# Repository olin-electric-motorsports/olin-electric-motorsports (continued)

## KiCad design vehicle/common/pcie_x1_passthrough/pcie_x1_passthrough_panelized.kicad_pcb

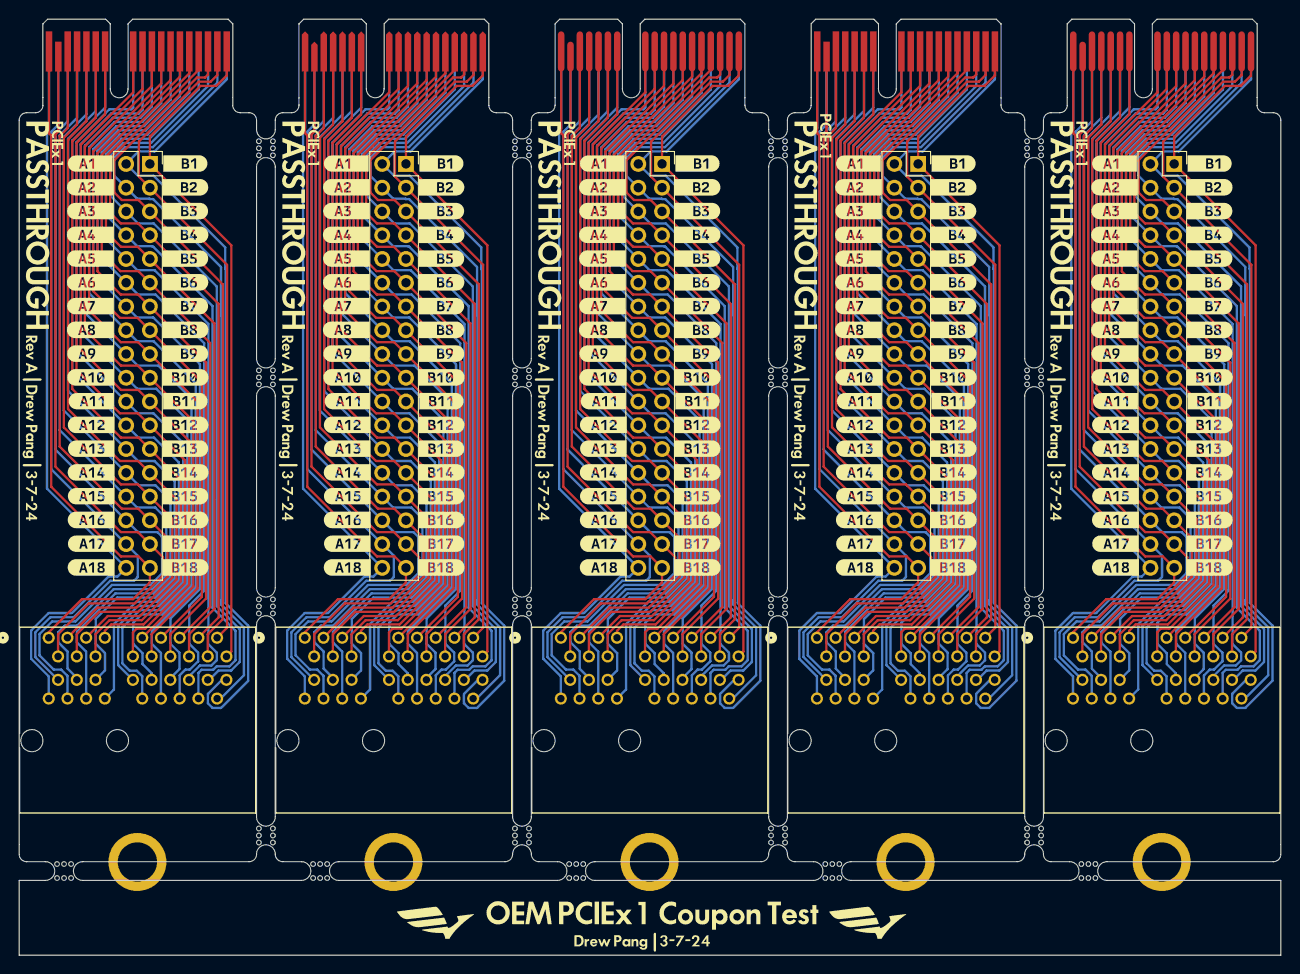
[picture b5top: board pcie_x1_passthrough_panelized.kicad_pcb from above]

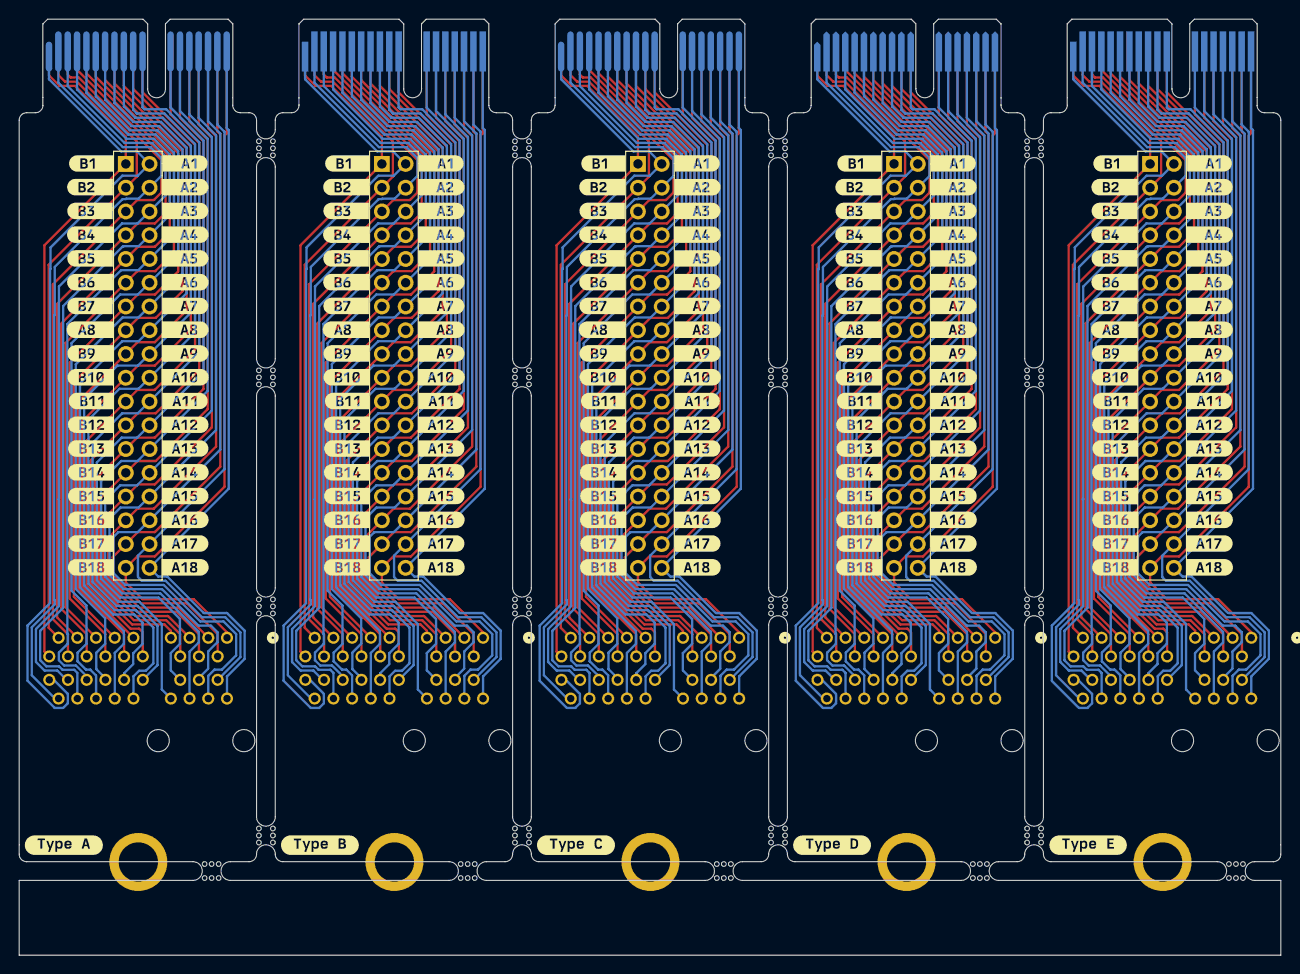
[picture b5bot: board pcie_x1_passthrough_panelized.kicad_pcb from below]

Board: 2 copper layers, 134.9 x 100.1 mm, 423 parts (190 on the bottom side), 36 nets.

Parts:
J1, J4, J8, J12, J16: pcie_x1_connector; pcie_x1_socket
J2, J2#2, J5, J6, J9, J10, J13, J14, J17, J18: Conn_02x18_Top_Bottom; PinSocket_2x18_P2.54mm_Vertical
J3, J7, J11, J11#2, J15: pcie_x1_connector; BUS_PCIexpress_x1
kibuzzard-65E1, kibuzzard-65E20, kibuzzard-65E39, kibuzzard-65E58, kibuzzard-65E96100: G***; kibuzzard-65E96100
kibuzzard-65E2, kibuzzard-65E21, kibuzzard-65E40, kibuzzard-65E59, kibuzzard-65E96303: G***; kibuzzard-65E96303
kibuzzard-65E3, kibuzzard-65E22, kibuzzard-65E41, kibuzzard-65E60, kibuzzard-65E96310: G***; kibuzzard-65E96310
kibuzzard-65E4, kibuzzard-65E23, kibuzzard-65E42, kibuzzard-65E61, kibuzzard-65E96314: G***; kibuzzard-65E96314
kibuzzard-65E5, kibuzzard-65E24, kibuzzard-65E43, kibuzzard-65E62, kibuzzard-65E96318: G***; kibuzzard-65E96318
kibuzzard-65E6, kibuzzard-65E25, kibuzzard-65E44, kibuzzard-65E63, kibuzzard-65E96322: G***; kibuzzard-65E96322
kibuzzard-65E7, kibuzzard-65E26, kibuzzard-65E45, kibuzzard-65E64, kibuzzard-65E96383: G***; kibuzzard-65E96383
kibuzzard-65E8, kibuzzard-65E27, kibuzzard-65E46, kibuzzard-65E65, kibuzzard-65E96396: G***; kibuzzard-65E96396
kibuzzard-65E9, kibuzzard-65E28, kibuzzard-65E47, kibuzzard-65E66, kibuzzard-65E96959: G***; kibuzzard-65E96959
kibuzzard-65E10, kibuzzard-65E29, kibuzzard-65E48, kibuzzard-65E67, kibuzzard-65E96962: G***; kibuzzard-65E96962
kibuzzard-65E11, kibuzzard-65E30, kibuzzard-65E49, kibuzzard-65E68, kibuzzard-65E96967: G***; kibuzzard-65E96967
kibuzzard-65E12, kibuzzard-65E31, kibuzzard-65E50, kibuzzard-65E69, kibuzzard-65E96973: G***; kibuzzard-65E96973
kibuzzard-65E13, kibuzzard-65E32, kibuzzard-65E51, kibuzzard-65E70, kibuzzard-65E96977: G***; kibuzzard-65E96977
kibuzzard-65E14, kibuzzard-65E33, kibuzzard-65E52, kibuzzard-65E71, kibuzzard-65E96980: G***; kibuzzard-65E96980
kibuzzard-65E15, kibuzzard-65E34, kibuzzard-65E53, kibuzzard-65E72, kibuzzard-65E96984: G***; kibuzzard-65E96984
kibuzzard-65E16, kibuzzard-65E35, kibuzzard-65E54, kibuzzard-65E73, kibuzzard-65E96989: G***; kibuzzard-65E96989
kibuzzard-65E17, kibuzzard-65E36, kibuzzard-65E55, kibuzzard-65E74, kibuzzard-65E96991: G***; kibuzzard-65E96991
kibuzzard-65E18, kibuzzard-65E37, kibuzzard-65E56, kibuzzard-65E75, kibuzzard-65E96995: G***; kibuzzard-65E96995
kibuzzard-65E19, kibuzzard-65E38, kibuzzard-65E57, kibuzzard-65E76, kibuzzard-65E96999: G***; kibuzzard-65E96999
kibuzzard-65E95D1, kibuzzard-65E95D2, kibuzzard-65E95D3, kibuzzard-65E95D4, kibuzzard-65E95D19: G***; kibuzzard-65E95D19
kibuzzard-65E95DA1, kibuzzard-65E95DA2, kibuzzard-65E95DA3, kibuzzard-65E95DA4, kibuzzard-65E95DA8: G***; kibuzzard-65E95DA8
kibuzzard-65E95DDF, kibuzzard-65E95DDF1, kibuzzard-65E95DDF2, kibuzzard-65E95DDF3, kibuzzard-65E95DDF4, kibuzzard-65E95DDF5, kibuzzard-65E95DDF6, kibuzzard-65E95DDF7, kibuzzard-65E95DDF8, kibuzzard-65E95DDF#2: G***; kibuzzard-65E95DDF
kibuzzard-65E95DE1, kibuzzard-65E95DE2, kibuzzard-65E95DE3, kibuzzard-65E95DE4, kibuzzard-65E95DE5: G***; kibuzzard-65E95DE4
kibuzzard-65E95DEB, kibuzzard-65E95DEB1, kibuzzard-65E95DEB2, kibuzzard-65E95DEB3, kibuzzard-65E95DEB4: G***; kibuzzard-65E95DEB
kibuzzard-65E95DEF, kibuzzard-65E95DEF1, kibuzzard-65E95DEF2, kibuzzard-65E95DEF3, kibuzzard-65E95DEF4: G***; kibuzzard-65E95DEF
kibuzzard-65E95DF1, kibuzzard-65E95DF3, kibuzzard-65E95DF4, kibuzzard-65E95DF6, kibuzzard-65E95DF9: G***; kibuzzard-65E95DF3
kibuzzard-65E95DF2, kibuzzard-65E95DF5, kibuzzard-65E95DF7, kibuzzard-65E95DF8, kibuzzard-65E95DF10: G***; kibuzzard-65E95DF8
kibuzzard-65E95DFB, kibuzzard-65E95DFB1, kibuzzard-65E95DFB2, kibuzzard-65E95DFB3, kibuzzard-65E95DFB4: G***; kibuzzard-65E95DFB
kibuzzard-65E95E1, kibuzzard-65E95E4, kibuzzard-65E95E04, kibuzzard-65E95E7, kibuzzard-65E95E10: G***; kibuzzard-65E95E04
kibuzzard-65E95E2, kibuzzard-65E95E5, kibuzzard-65E95E8, kibuzzard-65E95E11, kibuzzard-65E95E93: G***; kibuzzard-65E95E93
kibuzzard-65E95E3, kibuzzard-65E95E6, kibuzzard-65E95E9, kibuzzard-65E95E12, kibuzzard-65E95E97: G***; kibuzzard-65E95E97
kibuzzard-65E95E8F, kibuzzard-65E95E8F1, kibuzzard-65E95E8F2, kibuzzard-65E95E8F3, kibuzzard-65E95E8F4: G***; kibuzzard-65E95E8F
kibuzzard-65E95E9B, kibuzzard-65E95E9B1, kibuzzard-65E95E9B2, kibuzzard-65E95E9B3, kibuzzard-65E95E9B4: G***; kibuzzard-65E95E9B
kibuzzard-65E95E9E, kibuzzard-65E95E9E1, kibuzzard-65E95E9E2, kibuzzard-65E95E9E3, kibuzzard-65E95E9E4: G***; kibuzzard-65E95E9E
kibuzzard-65E95EA1, kibuzzard-65E95EA2, kibuzzard-65E95EA4, kibuzzard-65E95EA6, kibuzzard-65E95EA9: G***; kibuzzard-65E95EA2
kibuzzard-65E95EA3, kibuzzard-65E95EA5, kibuzzard-65E95EA7, kibuzzard-65E95EA8, kibuzzard-65E95EA10: G***; kibuzzard-65E95EA8
kibuzzard-65E95EAD, kibuzzard-65E95EAD1, kibuzzard-65E95EAD2, kibuzzard-65E95EAD3, kibuzzard-65E95EAD4: G***; kibuzzard-65E95EAD
kibuzzard-65E95F1, kibuzzard-65E95F2, kibuzzard-65E95F03, kibuzzard-65E95F3, kibuzzard-65E95F4: G***; kibuzzard-65E95F03
kibuzzard-65E960EE, kibuzzard-65E960EE1, kibuzzard-65E960EE2, kibuzzard-65E960EE3, kibuzzard-65E960EE4: G***; kibuzzard-65E960EE
kibuzzard-65E962FB, kibuzzard-65E962FB1, kibuzzard-65E962FB2, kibuzzard-65E962FB3, kibuzzard-65E962FB4: G***; kibuzzard-65E962FB
kibuzzard-65E962FE, kibuzzard-65E962FE1, kibuzzard-65E962FE2, kibuzzard-65E962FE3, kibuzzard-65E962FE4: G***; kibuzzard-65E962FE
kibuzzard-65E963A1, kibuzzard-65E963A3, kibuzzard-65E963A4, kibuzzard-65E963A6, kibuzzard-65E963A8: G***; kibuzzard-65E963A3
kibuzzard-65E963A2, kibuzzard-65E963A5, kibuzzard-65E963A7, kibuzzard-65E963A9, kibuzzard-65E963A10: G***; kibuzzard-65E963A9
kibuzzard-65E963AE, kibuzzard-65E963AE1, kibuzzard-65E963AE2, kibuzzard-65E963AE3, kibuzzard-65E963AE4: G***; kibuzzard-65E963AE
kibuzzard-65E969A0, kibuzzard-65E969A1, kibuzzard-65E969A3, kibuzzard-65E969A6, kibuzzard-65E969A8: G***; kibuzzard-65E969A0
kibuzzard-65E969A2, kibuzzard-65E969A4, kibuzzard-65E969A5, kibuzzard-65E969A7, kibuzzard-65E969A9: G***; kibuzzard-65E969A4
kibuzzard-65E969AA, kibuzzard-65E969AA1, kibuzzard-65E969AA2, kibuzzard-65E969AA3, kibuzzard-65E969AA4: G***; kibuzzard-65E969AA
kibuzzard-65E969AE, kibuzzard-65E969AE1, kibuzzard-65E969AE2, kibuzzard-65E969AE3, kibuzzard-65E969AE4: G***; kibuzzard-65E969AE
kibuzzard-65E969B1, kibuzzard-65E969B2, kibuzzard-65E969B4, kibuzzard-65E969B7, kibuzzard-65E969B9: G***; kibuzzard-65E969B1
kibuzzard-65E969B3, kibuzzard-65E969B5, kibuzzard-65E969B6, kibuzzard-65E969B8, kibuzzard-65E969B10: G***; kibuzzard-65E969B6
kibuzzard-65E969BA, kibuzzard-65E969BA1, kibuzzard-65E969BA2, kibuzzard-65E969BA3, kibuzzard-65E969BA4: G***; kibuzzard-65E969BA
kibuzzard-65E969BF, kibuzzard-65E969BF1, kibuzzard-65E969BF2, kibuzzard-65E969BF3, kibuzzard-65E969BF4: G***; kibuzzard-65E969BF
kibuzzard-65E969C1, kibuzzard-65E969C2, kibuzzard-65E969C4, kibuzzard-65E969C7, kibuzzard-65E969C9: G***; kibuzzard-65E969C2
kibuzzard-65E969C3, kibuzzard-65E969C5, kibuzzard-65E969C6, kibuzzard-65E969C8, kibuzzard-65E969C10: G***; kibuzzard-65E969C6
kibuzzard-65E969CA, kibuzzard-65E969CA1, kibuzzard-65E969CA2, kibuzzard-65E969CA3, kibuzzard-65E969CA4: G***; kibuzzard-65E969CA
kibuzzard-65E969CE, kibuzzard-65E969CE1, kibuzzard-65E969CE2, kibuzzard-65E969CE3, kibuzzard-65E969CE4: G***; kibuzzard-65E969CE
kibuzzard-65E969D1, kibuzzard-65E969D2, kibuzzard-65E969D4, kibuzzard-65E969D7, kibuzzard-65E969D9: G***; kibuzzard-65E969D2
kibuzzard-65E969D3, kibuzzard-65E969D5, kibuzzard-65E969D6, kibuzzard-65E969D8, kibuzzard-65E969D10: G***; kibuzzard-65E969D5
kibuzzard-65E969DA, kibuzzard-65E969DA1, kibuzzard-65E969DA2, kibuzzard-65E969DA3, kibuzzard-65E969DA4: G***; kibuzzard-65E969DA
kibuzzard-65E969DD, kibuzzard-65E969DD1, kibuzzard-65E969DD2, kibuzzard-65E969DD3, kibuzzard-65E969DD4: G***; kibuzzard-65E969DD
kibuzzard-65E969E1, kibuzzard-65E969E2, kibuzzard-65E969E6, kibuzzard-65E969E10, kibuzzard-65E969E13: G***; kibuzzard-65E969E1
kibuzzard-65E969E3, kibuzzard-65E969E5, kibuzzard-65E969E7, kibuzzard-65E969E11, kibuzzard-65E969E14: G***; kibuzzard-65E969E5
kibuzzard-65E969E4, kibuzzard-65E969E8, kibuzzard-65E969E9, kibuzzard-65E969E12, kibuzzard-65E969E15: G***; kibuzzard-65E969E9
kibuzzard-65E969ED, kibuzzard-65E969ED1, kibuzzard-65E969ED2, kibuzzard-65E969ED3, kibuzzard-65E969ED4: G***; kibuzzard-65E969ED
kibuzzard-65E981B7: G***; kibuzzard-65E981B7
kibuzzard-65E981F8: G***; kibuzzard-65E981F8
kibuzzard-65E981FF: G***; kibuzzard-65E981FF
kibuzzard-65E982B9: G***; kibuzzard-65E982B9
kibuzzard-65E9630A, kibuzzard-65E9630A1, kibuzzard-65E9630A2, kibuzzard-65E9630A3, kibuzzard-65E9630A4: G***; kibuzzard-65E9630A
kibuzzard-65E9633C, kibuzzard-65E9633C1, kibuzzard-65E9633C2, kibuzzard-65E9633C3, kibuzzard-65E9633C4: G***; kibuzzard-65E9633C
kibuzzard-65E9636C, kibuzzard-65E9636C1, kibuzzard-65E9636C2, kibuzzard-65E9636C3, kibuzzard-65E9636C4: G***; kibuzzard-65E9636C
kibuzzard-65E9638D, kibuzzard-65E9638D1, kibuzzard-65E9638D2, kibuzzard-65E9638D3, kibuzzard-65E9638D4: G***; kibuzzard-65E9638D
kibuzzard-65E9639B, kibuzzard-65E9639B1, kibuzzard-65E9639B2, kibuzzard-65E9639B3, kibuzzard-65E9639B4: G***; kibuzzard-65E9639B
kibuzzard-65E9639F, kibuzzard-65E9639F1, kibuzzard-65E9639F2, kibuzzard-65E9639F3, kibuzzard-65E9639F4: G***; kibuzzard-65E9639F
kibuzzard-65E9696D, kibuzzard-65E9696D1, kibuzzard-65E9696D2, kibuzzard-65E9696D3, kibuzzard-65E9696D4: G***; kibuzzard-65E9696D
kibuzzard-65E9697B, kibuzzard-65E9697B1, kibuzzard-65E9697B2, kibuzzard-65E9697B3, kibuzzard-65E9697B4: G***; kibuzzard-65E9697B
kibuzzard-65E9698D, kibuzzard-65E9698D1, kibuzzard-65E9698D2, kibuzzard-65E9698D3, kibuzzard-65E9698D4: G***; kibuzzard-65E9698D
kibuzzard-65E9699C, kibuzzard-65E9699C1, kibuzzard-65E9699C2, kibuzzard-65E9699C3, kibuzzard-65E9699C4: G***; kibuzzard-65E9699C
kibuzzard-65E98203: G***; kibuzzard-65E98203
kibuzzard-65E98207: G***; kibuzzard-65E98207
kibuzzard-65E98285: G***; kibuzzard-65E98285
mouse-bite-2mm-slot, mouse-bite-2mm-slot1, mouse-bite-2mm-slot2, mouse-bite-2mm-slot3, mouse-bite-2mm-slot4, mouse-bite-2mm-slot5, mouse-bite-2mm-slot6, mouse-bite-2mm-slot7, mouse-bite-2mm-slot8, mouse-bite-2mm-slot9, mouse-bite-2mm-slot10, mouse-bite-2mm-slot11, mouse-bite-2mm-slot12, mouse-bite-2mm-slot13, mouse-bite-2mm-slot14, mouse-bite-2mm-slot15, mouse-bite-2mm-slot15#2, mouse-bite-2mm-slot16, mouse-bite-2mm-slot17, mouse-bite-2mm-slot18, mouse-bite-2mm-slot19: VAL**; mouse-bite-2mm-slot

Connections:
/a1: J1.A1, J2.1, J3.A1, J4.A1, J5.1, J7.A1, J8.A1, J9.1, J11.A1, J12.A1, J13.1, J15.A1, J16.A1, J17.1
/a2: J1.A2, J2.2, J3.A2, J4.A2, J5.2, J7.A2, J8.A2, J9.2, J11.A2, J12.A2, J13.2, J15.A2, J16.A2, J17.2
/a3: J1.A3, J2.3, J3.A3, J4.A3, J5.3, J7.A3, J8.A3, J9.3, J11.A3, J12.A3, J13.3, J15.A3, J16.A3, J17.3
/a4: J1.A4, J2.4, J3.A4, J4.A4, J5.4, J7.A4, J8.A4, J9.4, J11.A4, J12.A4, J13.4, J15.A4, J16.A4, J17.4
/a5: J1.A5, J2.5, J3.A5, J4.A5, J5.5, J7.A5, J8.A5, J9.5, J11.A5, J12.A5, J13.5, J15.A5, J16.A5, J17.5
/a6: J1.A6, J2.6, J3.A6, J4.A6, J5.6, J7.A6, J8.A6, J9.6, J11.A6, J12.A6, J13.6, J15.A6, J16.A6, J17.6
/a7: J1.A7, J2.7, J3.A7, J4.A7, J5.7, J7.A7, J8.A7, J9.7, J11.A7, J12.A7, J13.7, J15.A7, J16.A7, J17.7
/a8: J1.A8, J2.8, J3.A8, J4.A8, J5.8, J7.A8, J8.A8, J9.8, J11.A8, J12.A8, J13.8, J15.A8, J16.A8, J17.8
/a9: J1.A9, J2.9, J3.A9, J4.A9, J5.9, J7.A9, J8.A9, J9.9, J11.A9, J12.A9, J13.9, J15.A9, J16.A9, J17.9
/a10: J1.A10, J2.10, J3.A10, J4.A10, J5.10, J7.A10, J8.A10, J9.10, J11.A10, J12.A10, J13.10, J15.A10, J16.A10, J17.10
/a11: J1.A11, J2.11, J3.A11, J4.A11, J5.11, J7.A11, J8.A11, J9.11, J11.A11, J12.A11, J13.11, J15.A11, J16.A11, J17.11
/a12: J1.A12, J2.12, J3.A12, J4.A12, J5.12, J7.A12, J8.A12, J9.12, J11.A12, J12.A12, J13.12, J15.A12, J16.A12, J17.12
/a13: J1.A13, J2.13, J3.A13, J4.A13, J5.13, J7.A13, J8.A13, J9.13, J11.A13, J12.A13, J13.13, J15.A13, J16.A13, J17.13
/a14: J1.A14, J2.14, J3.A14, J4.A14, J5.14, J7.A14, J8.A14, J9.14, J11.A14, J12.A14, J13.14, J15.A14, J16.A14, J17.14
/a15: J1.A15, J2.15, J3.A15, J4.A15, J5.15, J7.A15, J8.A15, J9.15, J11.A15, J12.A15, J13.15, J15.A15, J16.A15, J17.15
/a16: J1.A16, J2.16, J3.A16, J4.A16, J5.16, J7.A16, J8.A16, J9.16, J11.A16, J12.A16, J13.16, J15.A16, J16.A16, J17.16
/a17: J1.A17, J2.17, J3.A17, J4.A17, J5.17, J7.A17, J8.A17, J9.17, J11.A17, J12.A17, J13.17, J15.A17, J16.A17, J17.17
/a18: J1.A18, J2.18, J3.A18, J4.A18, J5.18, J7.A18, J8.A18, J9.18, J11.A18, J12.A18, J13.18, J15.A18, J16.A18, J17.18
/b1: J1.B1, J2.19, J3.B1, J4.B1, J5.19, J7.B1, J8.B1, J9.19, J11.B1, J12.B1, J13.19, J15.B1, J16.B1, J17.19
/b2: J1.B2, J2.20, J3.B2, J4.B2, J5.20, J7.B2, J8.B2, J9.20, J11.B2, J12.B2, J13.20, J15.B2, J16.B2, J17.20
/b3: J1.B3, J2.21, J3.B3, J4.B3, J5.21, J7.B3, J8.B3, J9.21, J11.B3, J12.B3, J13.21, J15.B3, J16.B3, J17.21
/b4: J1.B4, J2.22, J3.B4, J4.B4, J5.22, J7.B4, J8.B4, J9.22, J11.B4, J12.B4, J13.22, J15.B4, J16.B4, J17.22
/b5: J1.B5, J2.23, J3.B5, J4.B5, J5.23, J7.B5, J8.B5, J9.23, J11.B5, J12.B5, J13.23, J15.B5, J16.B5, J17.23
/b6: J1.B6, J2.24, J3.B6, J4.B6, J5.24, J7.B6, J8.B6, J9.24, J11.B6, J12.B6, J13.24, J15.B6, J16.B6, J17.24
/b7: J1.B7, J2.25, J3.B7, J4.B7, J5.25, J7.B7, J8.B7, J9.25, J11.B7, J12.B7, J13.25, J15.B7, J16.B7, J17.25
/b8: J1.B8, J2.26, J3.B8, J4.B8, J5.26, J7.B8, J8.B8, J9.26, J11.B8, J12.B8, J13.26, J15.B8, J16.B8, J17.26
/b9: J1.B9, J2.27, J3.B9, J4.B9, J5.27, J7.B9, J8.B9, J9.27, J11.B9, J12.B9, J13.27, J15.B9, J16.B9, J17.27
/b10: J1.B10, J2.28, J3.B10, J4.B10, J5.28, J7.B10, J8.B10, J9.28, J11.B10, J12.B10, J13.28, J15.B10, J16.B10, J17.28
/b11: J1.B11, J2.29, J3.B11, J4.B11, J5.29, J7.B11, J8.B11, J9.29, J11.B11, J12.B11, J13.29, J15.B11, J16.B11, J17.29
/b12: J1.B12, J2.30, J3.B12, J4.B12, J5.30, J7.B12, J8.B12, J9.30, J11.B12, J12.B12, J13.30, J15.B12, J16.B12, J17.30
/b13: J1.B13, J2.31, J3.B13, J4.B13, J5.31, J7.B13, J8.B13, J9.31, J11.B13, J12.B13, J13.31, J15.B13, J16.B13, J17.31
/b14: J1.B14, J2.32, J3.B14, J4.B14, J5.32, J7.B14, J8.B14, J9.32, J11.B14, J12.B14, J13.32, J15.B14, J16.B14, J17.32
/b15: J1.B15, J2.33, J3.B15, J4.B15, J5.33, J7.B15, J8.B15, J9.33, J11.B15, J12.B15, J13.33, J15.B15, J16.B15, J17.33
/b16: J1.B16, J2.34, J3.B16, J4.B16, J5.34, J7.B16, J8.B16, J9.34, J11.B16, J12.B16, J13.34, J15.B16, J16.B16, J17.34
/b17: J1.B17, J2.35, J3.B17, J4.B17, J5.35, J7.B17, J8.B17, J9.35, J11.B17, J12.B17, J13.35, J15.B17, J16.B17, J17.35
/b18: J1.B18, J2.36, J3.B18, J4.B18, J5.36, J7.B18, J8.B18, J9.36, J11.B18, J12.B18, J13.36, J15.B18, J16.B18, J17.36

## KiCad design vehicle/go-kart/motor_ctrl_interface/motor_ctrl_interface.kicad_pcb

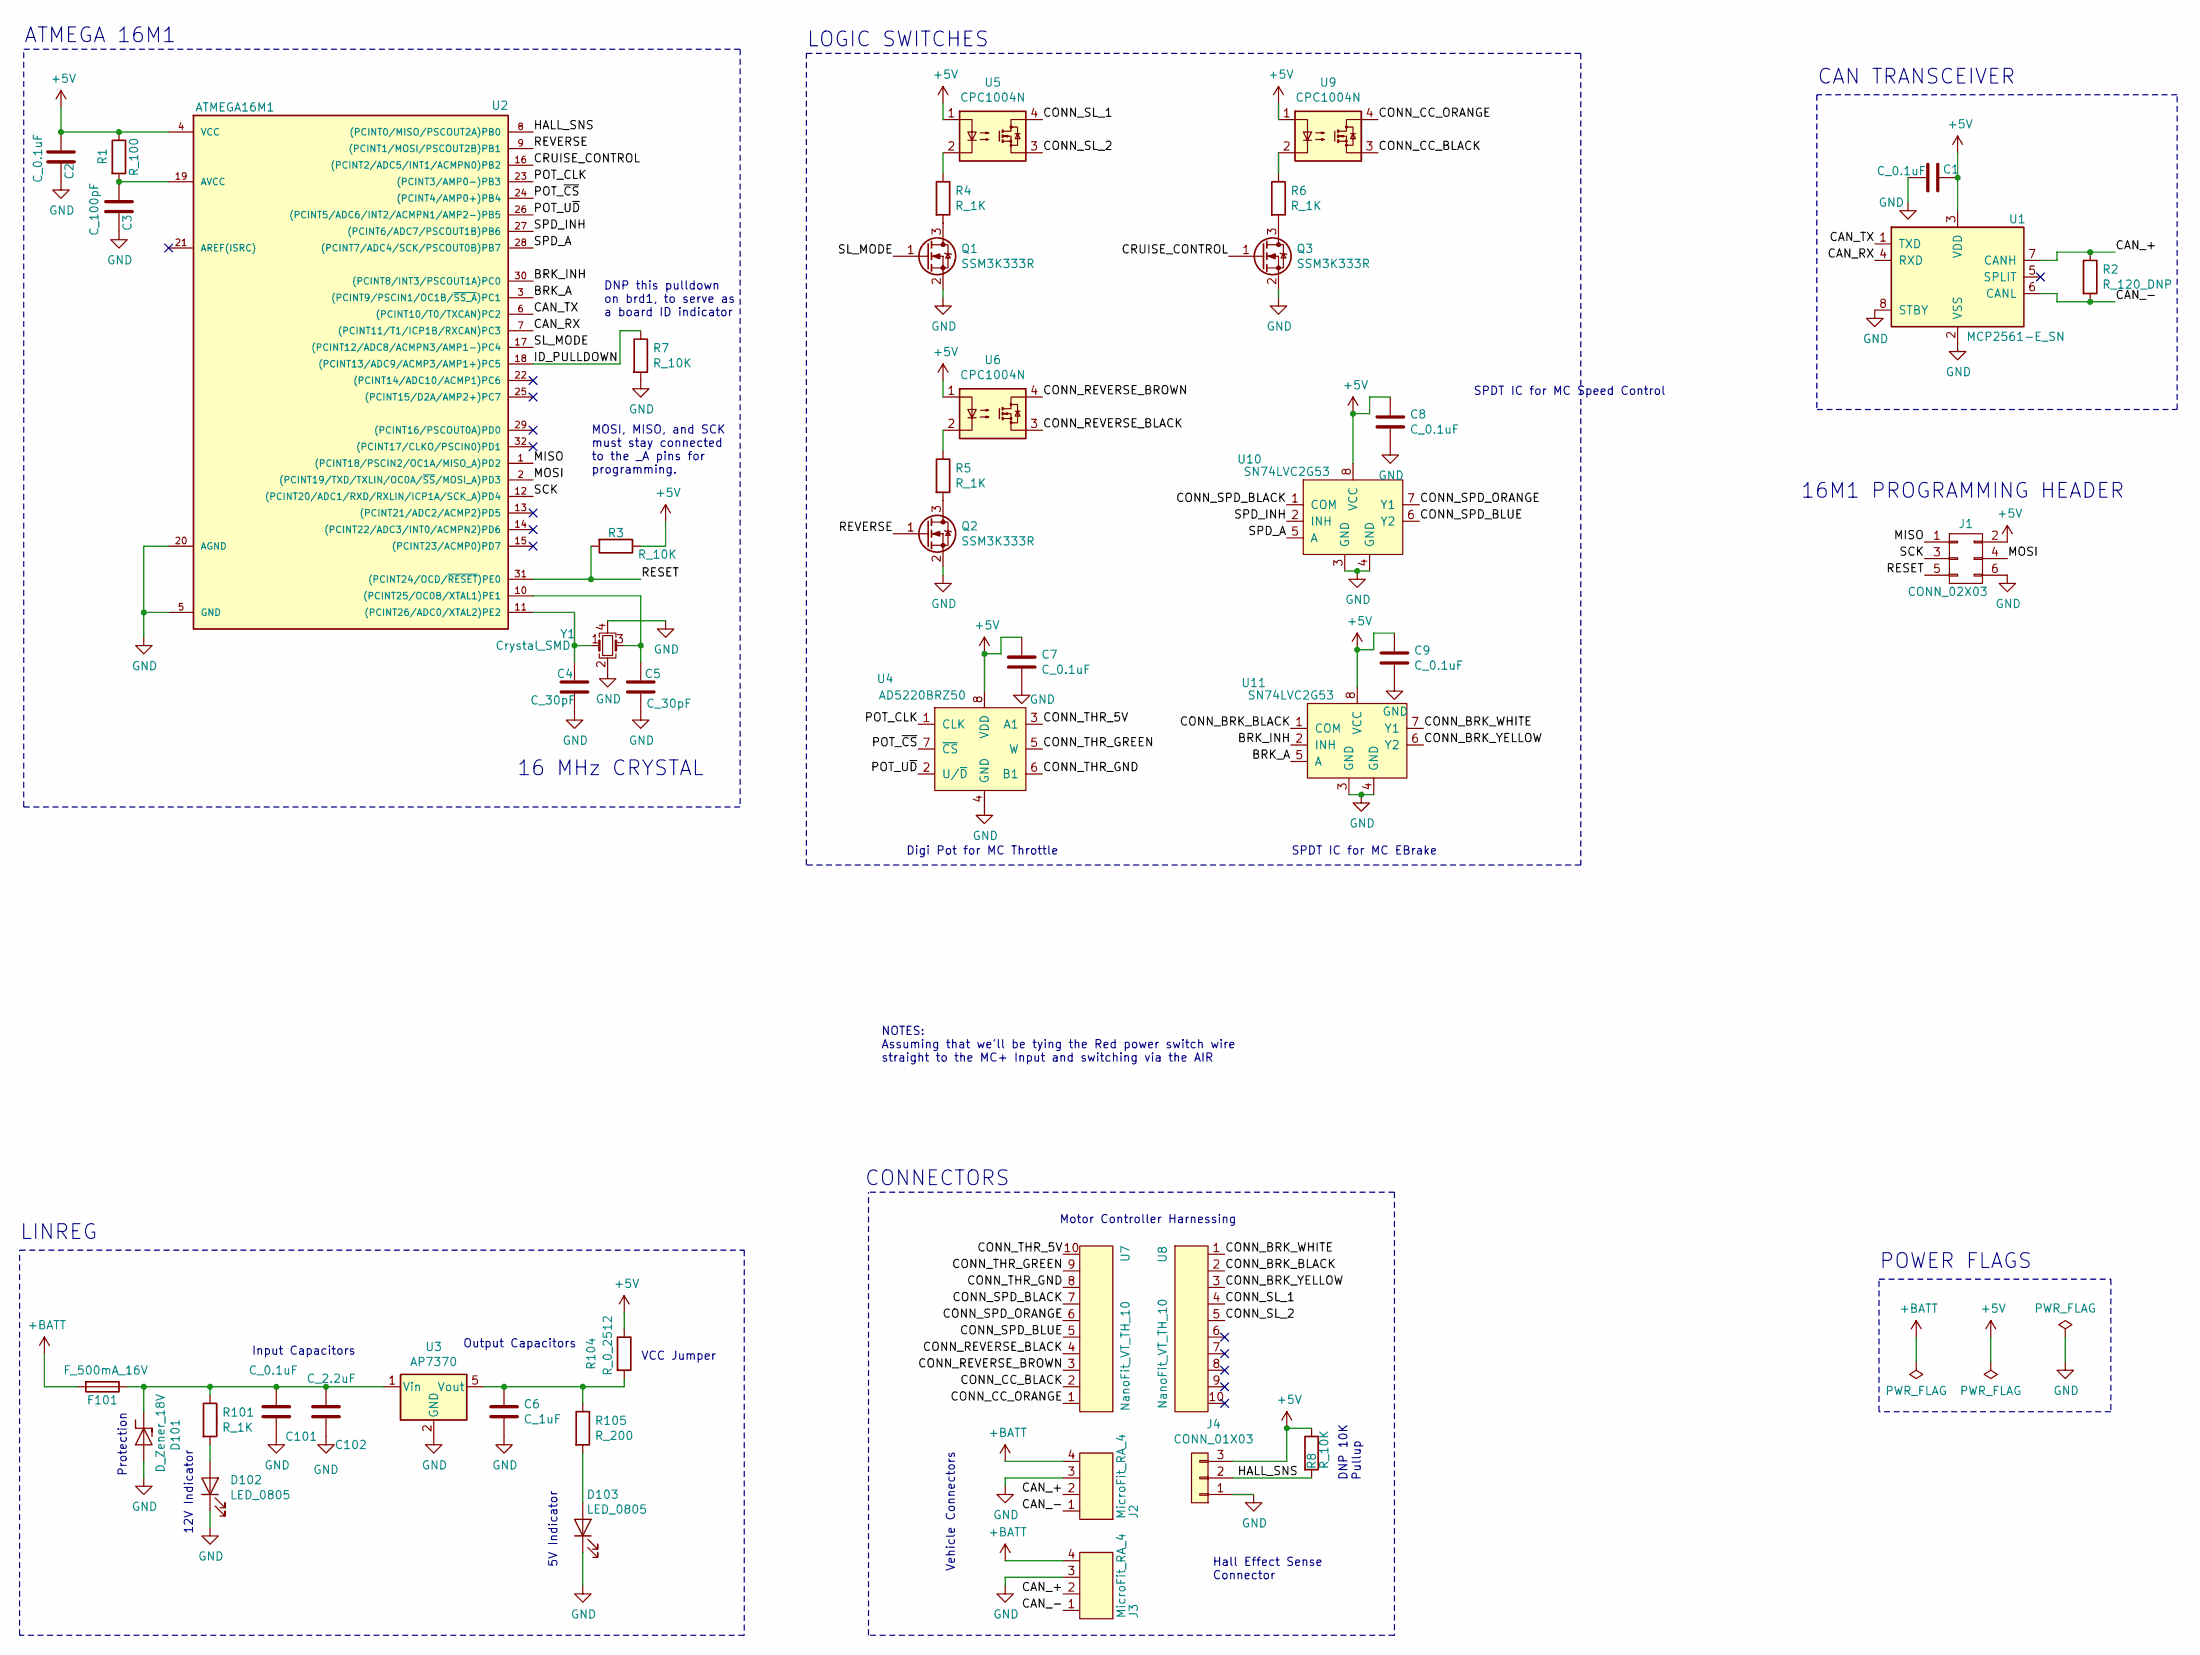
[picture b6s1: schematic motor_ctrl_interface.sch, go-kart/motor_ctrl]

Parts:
C1, C2, C7, C8, C9, C101: C_0.1uF; C_0805_OEM; MPN 478-3352-1-ND
C3: C_100pF; C_0805_OEM; MPN 732-7852-1-ND
C4, C5: C_30pF; C_0805_OEM; MPN 1276-1130-1-ND
C6: C_1uF; C_0805_OEM
C102: C_2.2uF; C_0603_1608Metric; MPN 311-1451-1-ND
D101: D_Zener_18V; DO-214AA; MPN SMBJ5355B-TPMSCT-ND
D102, D103: LED_0805; LED_0805_OEM; MPN 475-1410-1-ND
F101: F_500mA_16V; Fuse_1210; MPN 507-1786-1-ND
J1: CONN_02X03; Pin_Header_Straight_2x03; MPN 609-3234-ND
J2, J3: MicroFit_RA_4
J4: CONN_01X03; PinHeader_1x03_P2.54mm_Vertical; MPN 855-M20-9990346
Q1, Q2, Q3: SSM3K333R; SOT-23F; MPN SSM3K333RLFCT-ND
R1: R_100; R_0805_OEM; MPN RNCP0805FTD100RCT-ND
R2: R_120_DNP; R_0805_OEM; MPN 667-ERJ-6ENF1200V
R3, R7, R8: R_10K; R_0805_OEM; MPN CRS0805-FX-1002ELFCT-ND
R4, R5, R6, R101: R_1K; R_0805_OEM; MPN RNCP0805FTD1K00CT-ND
R104: R_0_2512; R_2512_OEM; MPN A121322CT-ND
R105: R_200; R_0805_OEM; MPN RMCF0805JT200RCT-ND
U1: MCP2561-E_SN; SOIC-8_3.9x4.9mm_Pitch1.27mm_OEM; MPN MCP2561-E/SN-ND
U2: ATMEGA16M1; TQFP-32_7x7mm_Pitch0.8mm; MPN ATMEGA16M1-AU-ND
U3: AP7370; SOT-23-5; MPN AP7370-50W5-7DICT-ND
U4: AD5220BRZ50; SOIC-8_3.9x4.9mm_Pitch1.27mm_OEM
U5, U6, U9: CPC1004N; SOP-4_3.8x4.1mm_P2.54mm
U7, U8: NanoFit_VT_TH_10; NanoFit_VT_10
U10, U11: SN74LVC2G53; MSOP-8_3x3mm_P0.65mm
Y1: Crystal_SMD; Crystal_SMD_FA238; MPN 887-1125-1-ND

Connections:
+5V: C1.1, C2.1, C7.1, C8.1, C9.1, J1.2, J4.3, R1.1, R3.1, R8.1, R104.1, U1.3 (VDD), U2.4 (VCC), U4.8 (VDD), U5.1, U6.1, U9.1, U10.8 (VCC), U11.8 (VCC)
+BATT: F101.2, J2.4, J3.4
/BRK_A: U2.3 ((PCINT9/PSCIN1/OC1B/~SS_A~)PC1), U11.5 (A)
/BRK_INH: U2.30 ((PCINT8/INT3/PSCOUT1A)PC0), U11.2 (INH)
/CAN_+: J2.2, J3.2, R2.1, U1.7 (CANH)
/CAN_-: J2.1, J3.1, R2.2, U1.6 (CANL)
/CAN_RX: U1.4 (RXD), U2.7 ((PCINT11/T1/ICP1B/RXCAN)PC3)
/CAN_TX: U1.1 (TXD), U2.6 ((PCINT10/T0/TXCAN)PC2)
/CONN_BRK_BLACK: U8.2, U11.1 (COM)
/CONN_BRK_WHITE: U8.1, U11.7 (Y1)
/CONN_BRK_YELLOW: U8.3, U11.6 (Y2)
/CONN_CC_BLACK: U7.2, U9.3
/CONN_CC_ORANGE: U7.1, U9.4
/CONN_REVERSE_BLACK: U6.3, U7.4
/CONN_REVERSE_BROWN: U6.4, U7.3
/CONN_SL_1: U5.4, U8.4
/CONN_SL_2: U5.3, U8.5
/CONN_SPD_BLACK: U7.7, U10.1 (COM)
/CONN_SPD_BLUE: U7.5, U10.6 (Y2)
/CONN_SPD_ORANGE: U7.6, U10.7 (Y1)
/CONN_THR_5V: U4.3 (A1), U7.10
/CONN_THR_GND: U4.6 (B1), U7.8
/CONN_THR_GREEN: U4.5 (W), U7.9
/CRUISE_CONTROL: Q3.1 (G), U2.16 ((PCINT2/ADC5/INT1/ACMPN0)PB2)
/HALL_SNS: J4.2, R8.2, U2.8 ((PCINT0/MISO/PSCOUT2A)PB0)
/ID_PULLDOWN: R7.1, U2.18 ((PCINT13/ADC9/ACMP3/AMP1+)PC5)
/MISO: J1.1, U2.1 ((PCINT18/PSCIN2/OC1A/MISO_A)PD2)
/MOSI: J1.4, U2.2 ((PCINT19/TXD/TXLIN/OC0A/~SS~/MOSI_A)PD3)
/POT_CLK: U2.23 ((PCINT3/AMP0-)PB3), U4.1 (CLK)
/POT_U~D: U2.26 ((PCINT5/ADC6/INT2/ACMPN1/AMP2-)PB5), U4.2 (U/~D)
/POT_~CS: U2.24 ((PCINT4/AMP0+)PB4), U4.7 (~CS)
/RESET: J1.5, R3.2, U2.31 ((PCINT24/OCD/~RESET~)PE0)
/REVERSE: Q2.1 (G), U2.9 ((PCINT1/MOSI/PSCOUT2B)PB1)
/SCK: J1.3, U2.12 ((PCINT20/ADC1/RXD/RXLIN/ICP1A/SCK_A)PD4)
/SL_MODE: Q1.1 (G), U2.17 ((PCINT12/ADC8/ACMPN3/AMP1-)PC4)
/SPD_A: U2.28 ((PCINT7/ADC4/SCK/PSCOUT0B)PB7), U10.5 (A)
/SPD_INH: U2.27 ((PCINT6/ADC7/PSCOUT1B)PB6), U10.2 (INH)
GND: C1.2, C2.2, C3.2, C4.2, C5.2, C6.2, C7.2, C8.2, C9.2, C101.2, C102.2, D101.2 (A), D102.1 (K), D103.1 (K), J1.6, J2.3, J3.3, J4.1, Q1.2 (S), Q2.2 (S), Q3.2 (S), R7.2, U1.2 (VSS), U1.8 (STBY), U2.5 (GND), U2.20 (AGND), U3.2 (GND), U4.4 (GND), U10.3 (GND), U10.4 (GND), U11.3 (GND), U11.4 (GND), Y1.2, Y1.4
unnamed: C3.1, R1.2, U2.19 (AVCC)
unnamed: C4.1, U2.11 ((PCINT26/ADC0/XTAL2)PE2), Y1.1
unnamed: C5.1, U2.10 ((PCINT25/OC0B/XTAL1)PE1), Y1.3
unnamed: C6.1, R104.2, R105.1, U3.5 (Vout)
unnamed: C101.1, C102.1, D101.1 (K), F101.1, R101.1, U3.1 (Vin)
unnamed: D102.2 (A), R101.2
unnamed: D103.2 (A), R105.2
unnamed: Q1.3 (D), R4.2
unnamed: Q2.3 (D), R5.2
unnamed: Q3.3 (D), R6.2
unnamed: R4.1, U5.2
unnamed: R5.1, U6.2
unnamed: R6.1, U9.2

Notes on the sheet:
Input Capacitors
12V Indicator
Protection
LINREG
Output Capacitors
VCC Jumper
5V Indicator
CAN TRANSCEIVER
ATMEGA 16M1
16 MHz CRYSTAL
POWER FLAGS
16M1 PROGRAMMING HEADER
MOSI, MISO, and SCK must stay connected to the _A pins for programming.
Digi Pot for MC Throttle
SPDT IC for MC Speed Control
SPDT IC for MC EBrake
Motor Controller Harnessing
Vehicle Connectors
CONNECTORS
LOGIC SWITCHES
DNP 10K Pullup
Hall Effect Sense Connector
NOTES: Assuming that we'll be tying the Red power switch wire straight to the MC+ Input and switching via the AIR
DNP this pulldown on brd1, to serve as a board ID indicator

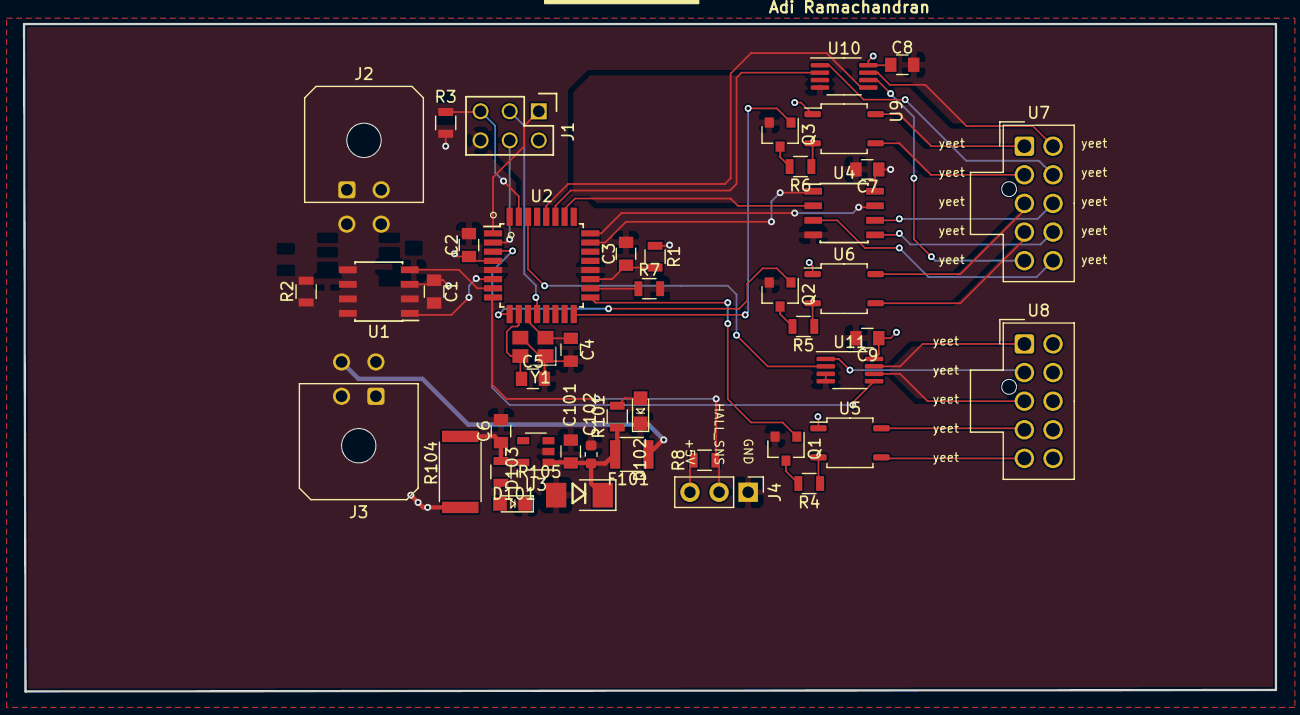
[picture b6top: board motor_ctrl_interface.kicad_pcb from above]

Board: 2 copper layers, 109.3 x 58.3 mm, 45 parts (0 on the bottom side), 51 nets.

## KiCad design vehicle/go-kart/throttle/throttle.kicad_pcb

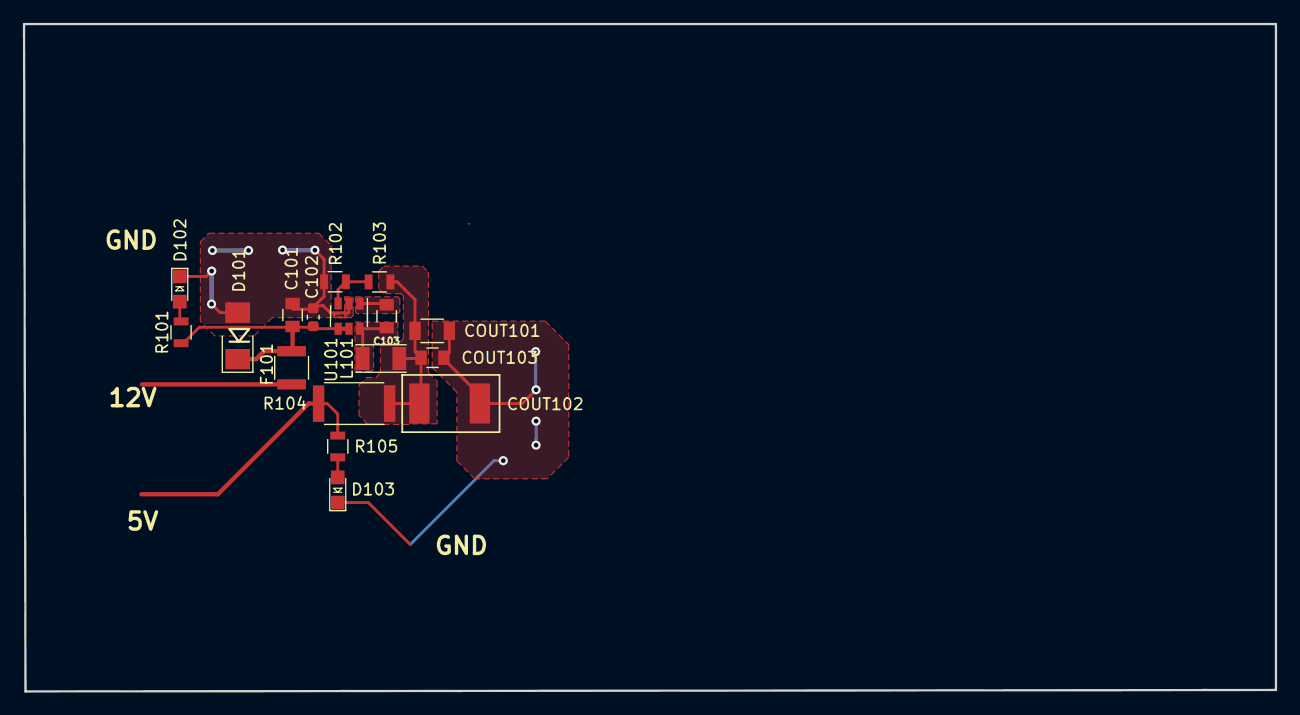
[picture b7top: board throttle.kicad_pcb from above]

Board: 2 copper layers, 109.3 x 58.3 mm, 17 parts (0 on the bottom side), 9 nets.

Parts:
C101, C103: C_0.1uF; C_0805_OEM
C102: C_2.2uF; C_0603_1608Metric
COUT101: C_22uF; C_1206_OEM
COUT102: C_33uF; Fuse_1812
COUT103: C_47uF; C_0805_OEM
D101: D_Zener_18V; DO-214AA
D102, D103: LED_0805; LED_0805_OEM
F101: F_500mA_16V; Fuse_1210
L101: L_100uH; L_100uH_OEM
R101: R_1K; R_0805_OEM
R102: R_25K; R_0805_OEM
R103: R_100K; R_0805_OEM
R104: R_0_2512; R_2512_OEM
R105: R_200; R_0805_OEM
U101: TPS560430YF; SOT-23-6_OEM

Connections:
GND: C101.2, C102.2, COUT101.2, COUT102.2, COUT103.2, D101.2, D102.1, D103.1, R102.2, U101.2
unnamed: C101.1, C102.1, D101.1, F101.1, R101.1, U101.4, U101.5
unnamed: C103.1, U101.1
unnamed: C103.2, L101.1, U101.6
unnamed: COUT101.1, COUT102.1, COUT103.1, L101.2, R103.1, R104.1
unnamed: D102.2, R101.2
unnamed: D103.2, R105.2
unnamed: R102.1, R103.2, U101.3
VCC: R104.2, R105.1

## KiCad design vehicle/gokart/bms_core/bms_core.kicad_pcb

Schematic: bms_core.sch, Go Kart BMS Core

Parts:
C1, C2: C_0.1uF; C_0805_OEM; MPN 478-3352-1-ND
C3: C_100pF; C_0805_OEM; MPN 732-7852-1-ND
C4, C5: C_30pF; C_0805_OEM; MPN 1276-1130-1-ND
C6, C7, C10: C_1uF; C_0805_OEM
C8, C9: C_10nF; C_1206_OEM; MPN C1206C103KCRACTU
D1, D2, D3, D4, D5, D6, D102, D103: LED_0805; LED_0805_OEM; MPN 475-1410-1-ND
D101: D_Zener_18V; DO-214AA; MPN SMBJ5355B-TPMSCT-ND
F101: F_500mA_16V; Fuse_1210; MPN 507-1786-1-ND
J1: CONN_02X03; Pin_Header_Straight_2x03; MPN 609-3234-ND
J2, J4: NanoFit_RA_TH_02; NanoFit_Molex_1x02x2.50mm_Angled_OEM; MPN WM14972-ND
J3, J5, J6, J7: MicroFit_RA_4
Q1, Q2, Q3, Q5: SSM3K333R; SOT-23F; MPN SSM3K333RLFCT-ND
Q4: SSM3J334R; SOT-23F; MPN SSM3J334R,LF
R1: R_100; R_0805_OEM; MPN RNCP0805FTD100RCT-ND
R2: R_120_DNP; R_0805_OEM; MPN 667-ERJ-6ENF1200V
R3, R5, R12, R14, R16, R17: R_10K; R_0805_OEM; MPN CRS0805-FX-1002ELFCT-ND
R4, R9, R10, R11, R13, R15, R105: R_200; R_0805_OEM; MPN RMCF0805JT200RCT-ND
R6, R18, R19, R101: R_1K; R_0805_OEM; MPN RNCP0805FTD1K00CT-ND
R7, R8: R_60.4; R_0805_OEM; MPN P60.4DACT-ND
R104: R_0_2512; R_2512_OEM; MPN A121322CT-ND
T1: T_LAN_SM91501ALE; MPN SM91501ALE
U1: MCP2561-E_SN; SOIC-8_3.9x4.9mm_Pitch1.27mm_OEM; MPN MCP2561-E/SN-ND
U2: ATMEGA16M1; TQFP-32_7x7mm_Pitch0.8mm; MPN ATMEGA16M1-AU-ND
U3: AP7370; SOT-23-5; MPN AP7370-50W5-7DICT-ND
U4: LTC6820HMS; MSOP-16_3x4mm_P0.5mm; MPN LTC6820HMS#TRPBFCT-ND
Y1: Crystal_SMD; Crystal_SMD_FA238; MPN 887-1125-1-ND

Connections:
+5V: C1.1, C2.1, C10.1, J1.2, J3.2, R1.1, R3.1, R4.1, R9.1, R10.1, R17.2, R104.1, U1.3 (VDD), U2.4 (VCC), U4.6 (VDDS), U4.7 (POL), U4.8 (PHA), U4.9 (VDD), U4.12 (MSTR)
+BATT: F101.2, J5.3, J6.2, J7.2, Q4.3, R19.1
/AIR_LSD: Q1.1 (G), R13.1, R14.1
/AIR_WELD: J3.1, R11.1, R12.1, U2.28 ((PCINT7/ADC4/SCK/PSCOUT0B)PB7)
/CAN_+: J6.4, J7.4, R2.1, U1.7 (CANH)
/CAN_-: J6.3, J7.3, R2.2, U1.6 (CANL)
/CAN_RX: U1.4 (RXD), U2.7 ((PCINT11/T1/ICP1B/RXCAN)PC3)
/CAN_TX: U1.1 (TXD), U2.6 ((PCINT10/T0/TXCAN)PC2)
/COIL_+: J3.4, J4.1, Q2.1 (G), R15.1, R16.1
/COIL_-: J3.3, Q1.3 (D)
/CS_iso: U2.16 ((PCINT2/ADC5/INT1/ACMPN0)PB2), U4.5 (~CS)
/DEBUG_1: D1.1 (K), U2.25 ((PCINT15/D2A/AMP2+)PC7)
/DEBUG_2: D2.1 (K), U2.26 ((PCINT5/ADC6/INT2/ACMPN1/AMP2-)PB5)
/DEBUG_3: D3.1 (K), U2.27 ((PCINT6/ADC7/PSCOUT1B)PB6)
/FAN_PWM: J5.2, Q4.2, Q5.3 (D)
/FAN_PWM_RAW: Q3.1 (G), R5.1, U2.3 ((PCINT9/PSCIN1/OC1B/~SS_A~)PC1)
/MISO: J1.1, U2.1 ((PCINT18/PSCIN2/OC1A/MISO_A)PD2)
/MISO_iso: U2.8 ((PCINT0/MISO/PSCOUT2A)PB0), U4.3 (MISO)
/MOSI: J1.4, U2.2 ((PCINT19/TXD/TXLIN/OC0A/~SS~/MOSI_A)PD3)
/MOSI_iso: U2.9 ((PCINT1/MOSI/PSCOUT2B)PB1), U4.2 (MOSI)
/RESET: J1.5, R3.2, U2.31 ((PCINT24/OCD/~RESET~)PE0)
/SCK: J1.3, U2.12 ((PCINT20/ADC1/RXD/RXLIN/ICP1A/SCK_A)PD4)
/SCK_iso: U2.23 ((PCINT3/AMP0-)PB3), U4.4 (SCK)
/SHUTDOWN_SENSE: Q2.3 (D), R17.1, U2.29 ((PCINT16/PSCOUT0A)PD0)
GND: C1.2, C2.2, C3.2, C4.2, C5.2, C6.2, C7.2, C8.2, C9.2, C10.2, D4.1 (K), D5.1 (K), D6.1 (K), D101.2 (A), D102.1 (K), D103.1 (K), J1.6, J4.2, J5.1, J6.1, J7.1, Q1.2 (S), Q2.2 (S), Q3.2 (S), Q5.2 (S), R5.2, R6.2, R12.2, R14.2, R16.2, U1.2 (VSS), U1.8 (STBY), U2.5 (GND), U2.20 (AGND), U3.2 (GND), U4.1 (EN), U4.13 (SLOW), U4.14 (GND), Y1.2, Y1.4
unnamed: C3.1, R1.2, U2.19 (AVCC)
unnamed: C4.1, U2.11 ((PCINT26/ADC0/XTAL2)PE2), Y1.1
unnamed: C5.1, U2.10 ((PCINT25/OC0B/XTAL1)PE1), Y1.3
unnamed: C6.1, D101.1 (K), F101.1, R101.1, U3.1 (Vin)
unnamed: C7.1, R104.2, R105.1, U3.5 (Vout)
unnamed: C8.1, R7.2, R8.1
unnamed: C9.1, T1.11
unnamed: D1.2 (A), R4.2
unnamed: D2.2 (A), R9.2
unnamed: D3.2 (A), R10.2
unnamed: D4.2 (A), R11.2
unnamed: D5.2 (A), R13.2
unnamed: D6.2 (A), R15.2
unnamed: D102.2 (A), R101.2
unnamed: D103.2 (A), R105.2
unnamed: J2.1, T1.1
unnamed: J2.2, T1.3
unnamed: Q3.3 (D), Q4.1, Q5.1 (G), R19.2
unnamed: R7.1, T1.12, U4.10 (IM)
unnamed: R8.2, T1.10, U4.11 (IP)
unnamed: R18.1, U4.16 (IBIAS)
unnamed: R6.1, R18.2, U4.15 (ICMP)

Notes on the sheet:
Input Capacitor
12V Indicator
Protection
5V LDO
Output Capacitor
VCC Jumper
5V Indicator
CAN TRANSCEIVER
ATMEGA 16M1
16 MHz CRYSTAL
POWER FLAGS
16M1 PROGRAMMING HEADER
MOSI, MISO, and SCK must stay connected to the _A pins for programming.
isoSPI INTERFACE
DEBUG LEDS
MAIN CONNECTORS
SHUTDOWN CONNECTOR
isoSPI connector
AIR CONNECTOR
HIGH when closed LOW when open
AIR WELD DETECTION
AIR LOW SIDE DRIVER
FAN PWM BUFFER
SHUTDOWN SENSE
FAN CONNECTOR
